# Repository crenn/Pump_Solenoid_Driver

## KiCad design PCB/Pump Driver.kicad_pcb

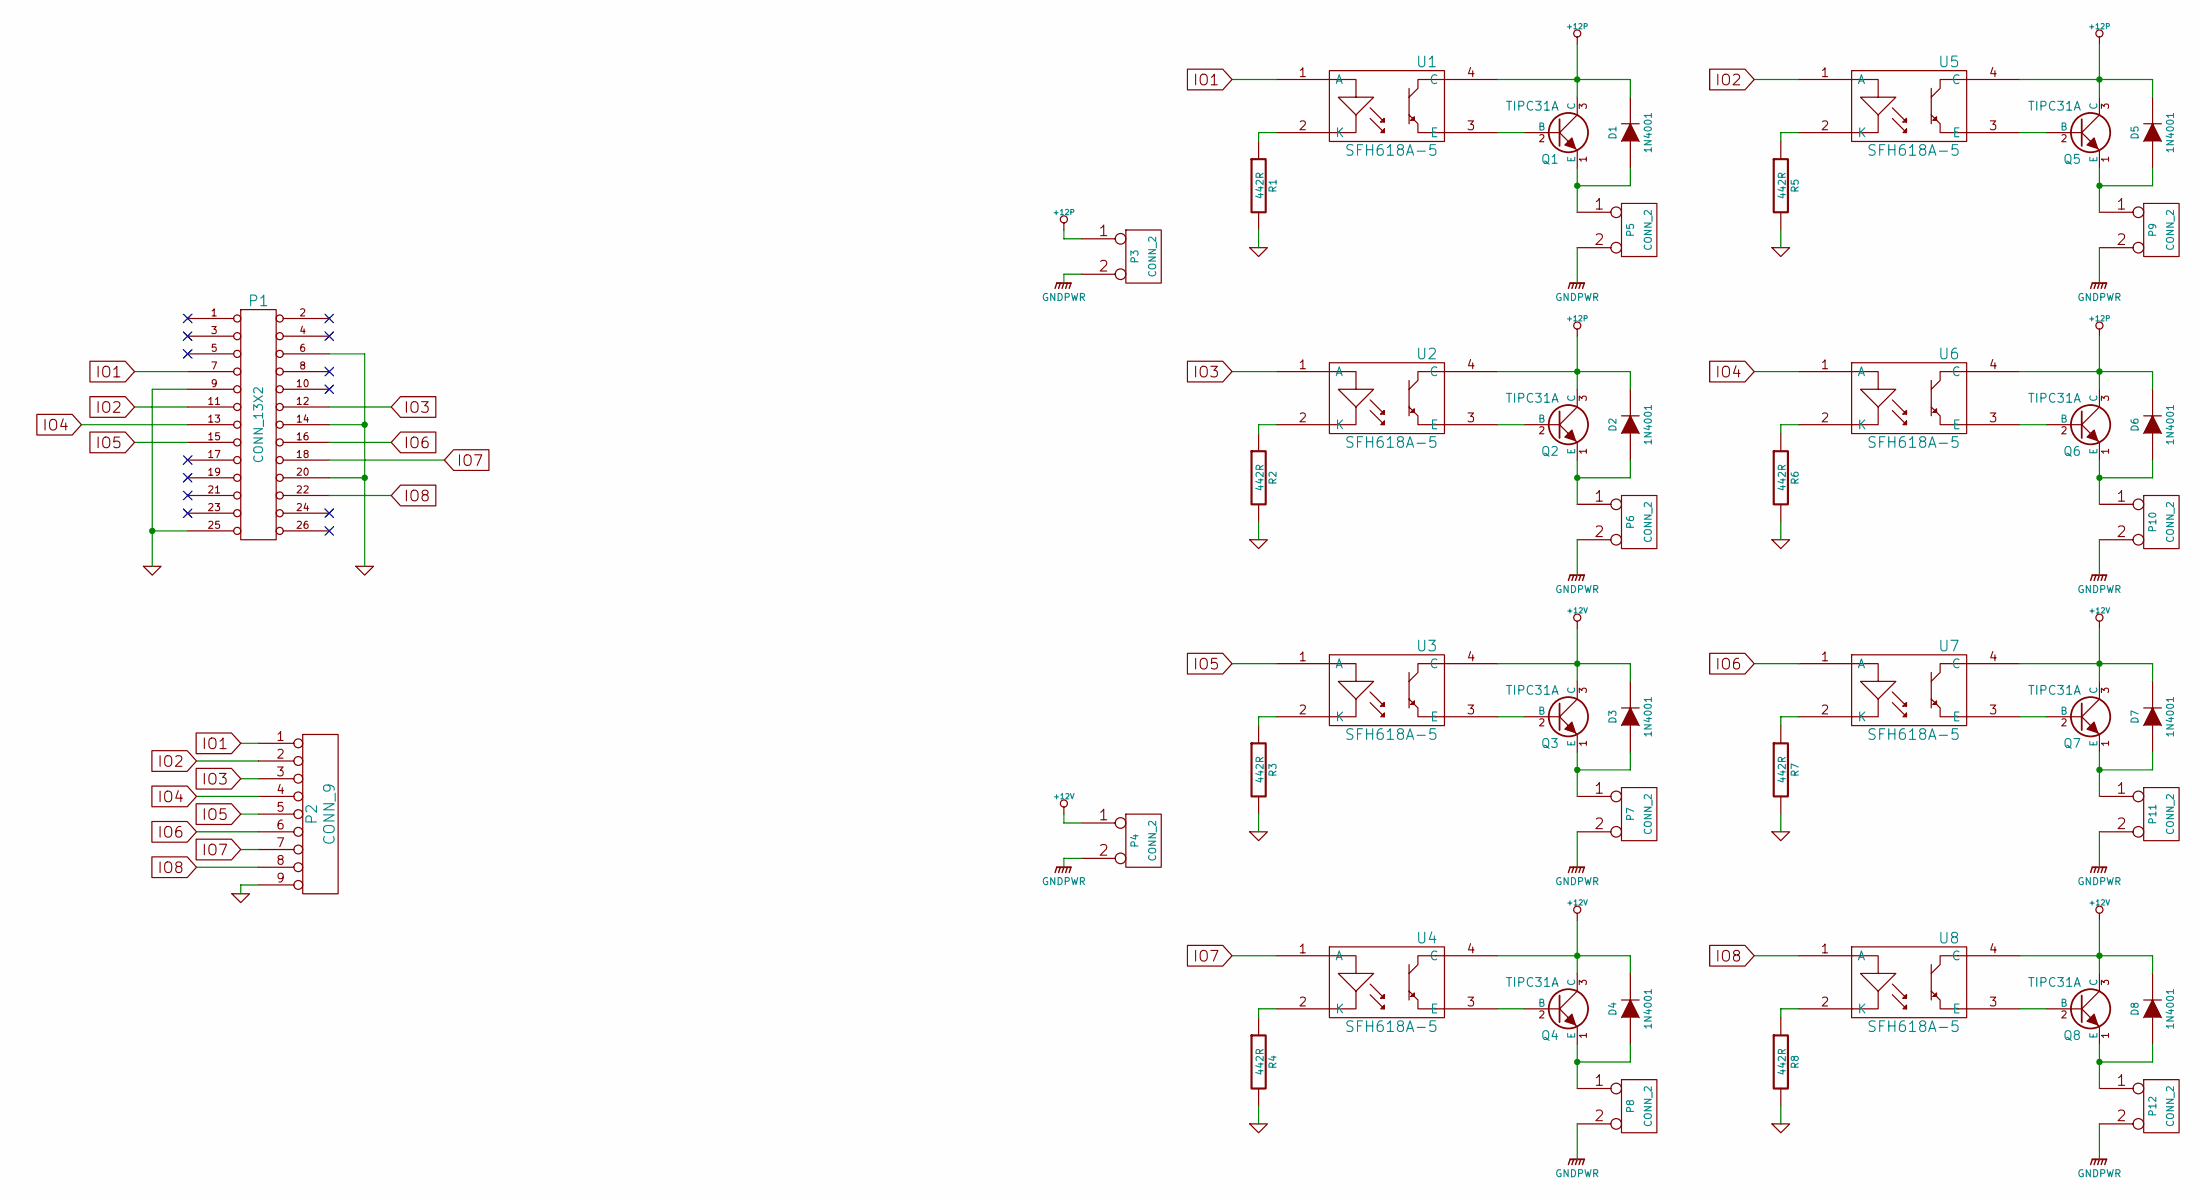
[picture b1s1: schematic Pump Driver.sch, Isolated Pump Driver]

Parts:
D1, D2, D3, D4, D5, D6, D7, D8: 1N4001
P1: CONN_13X2
P2: CONN_9
P3, P4, P5, P6, P7, P8, P9, P10, P11, P12: CONN_2
Q1, Q2, Q3, Q4, Q5, Q6, Q7, Q8: TIPC31A
R1, R2, R3, R4, R5, R6, R7, R8: 442R
U1, U2, U3, U4, U5, U6, U7, U8: SFH618A-5

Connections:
+12P: D1.2 (K), D2.2 (K), D5.2 (K), D6.2 (K), P3.1, Q1.3 (C), Q2.3 (C), Q5.3 (C), Q6.3 (C), U1.4 (C), U2.4 (C), U5.4 (C), U6.4 (C)
+12V: D3.2 (K), D4.2 (K), D7.2 (K), D8.2 (K), P4.1, Q3.3 (C), Q4.3 (C), Q7.3 (C), Q8.3 (C), U3.4 (C), U4.4 (C), U7.4 (C), U8.4 (C)
GND: P1.6, P1.9, P1.14, P1.20, P1.25 (P24), P2.9, R1.2, R2.2, R3.2, R4.2, R5.2, R6.2, R7.2, R8.2
GNDPWR: P3.2 (PM), P4.2 (PM), P5.2 (PM), P6.2 (PM), P7.2 (PM), P8.2 (PM), P9.2 (PM), P10.2 (PM), P11.2 (PM), P12.2 (PM)
IO1: P1.7, P2.1, U1.1 (A)
IO2: P1.11, P2.2, U5.1 (A)
IO3: P1.12, P2.3, U2.1 (A)
IO4: P1.13, P2.4, U6.1 (A)
IO5: P1.15, P2.5, U3.1 (A)
IO6: P1.16, P2.6, U7.1 (A)
IO7: P1.18, P2.7, U4.1 (A)
IO8: P1.22, P2.8, U8.1 (A)
unnamed: R7.1, U7.2 (K)
unnamed: D7.1 (A), P11.1, Q7.1 (E)
unnamed: Q7.2 (B), U7.3 (E)
unnamed: R8.1, U8.2 (K)
unnamed: D8.1 (A), P12.1, Q8.1 (E)
unnamed: Q8.2 (B), U8.3 (E)
unnamed: Q1.2 (B), U1.3 (E)
unnamed: R6.1, U6.2 (K)
unnamed: R2.1, U2.2 (K)
unnamed: Q2.2 (B), U2.3 (E)
unnamed: R5.1, U5.2 (K)
unnamed: Q5.2 (B), U5.3 (E)
unnamed: R4.1, U4.2 (K)
unnamed: Q4.2 (B), U4.3 (E)
unnamed: D3.1 (A), P7.1, Q3.1 (E)
unnamed: Q3.2 (B), U3.3 (E)
unnamed: R3.1, U3.2 (K)
unnamed: D4.1 (A), P8.1, Q4.1 (E)
unnamed: R1.1, U1.2 (K)
unnamed: D1.1 (A), P5.1, Q1.1 (E)
unnamed: D2.1 (A), P6.1, Q2.1 (E)
unnamed: D5.1 (A), P9.1, Q5.1 (E)
unnamed: Q6.2 (B), U6.3 (E)
unnamed: D6.1 (A), P10.1, Q6.1 (E)

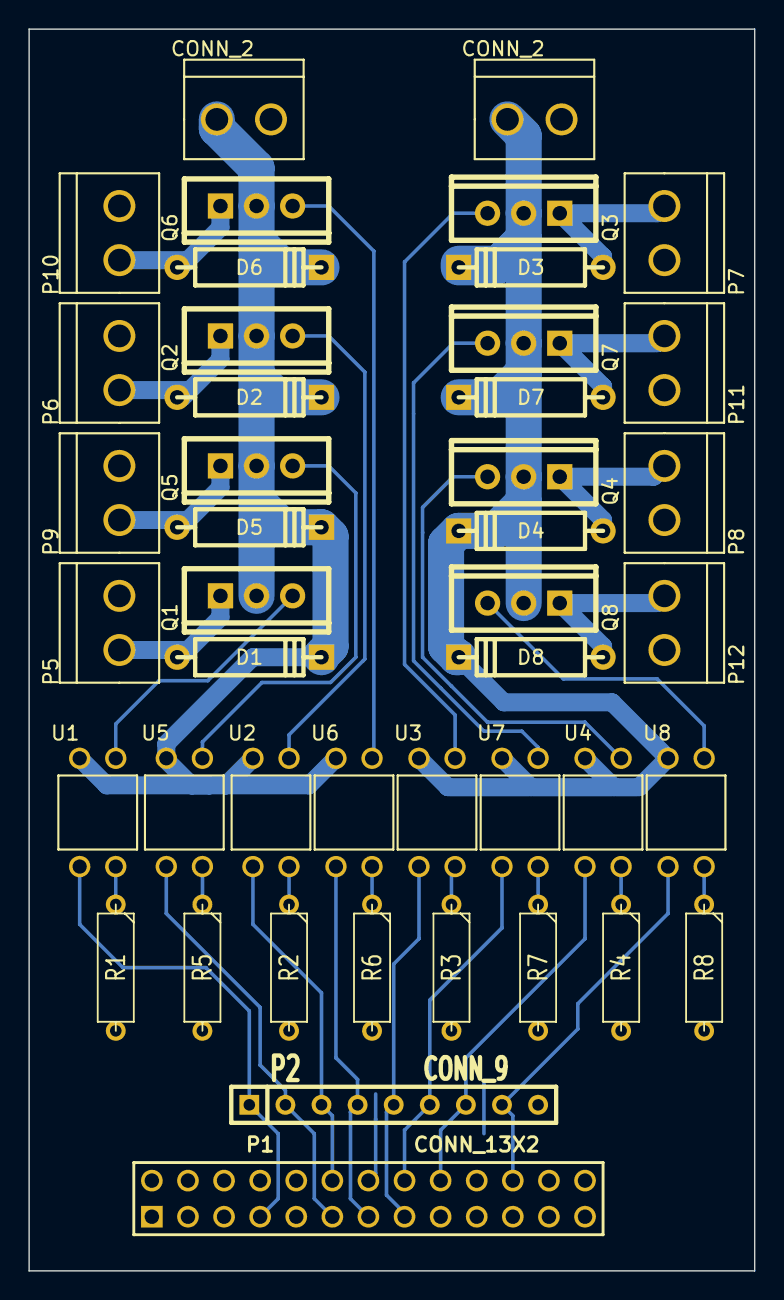
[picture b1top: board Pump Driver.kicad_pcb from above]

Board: 2 copper layers, 51.1 x 87.4 mm, 44 parts (0 on the bottom side), 36 nets.

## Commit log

2014-06-12 Initial Commit
    Basic Schematic for the driver, no values of components though
2014-06-18 Update schematic and start PCB layout
    Update schematic with part values and numbers, create netlist and part
    footprints, start component layout.
2014-06-20 Lay all tracks & ground plane. Correct schematic
